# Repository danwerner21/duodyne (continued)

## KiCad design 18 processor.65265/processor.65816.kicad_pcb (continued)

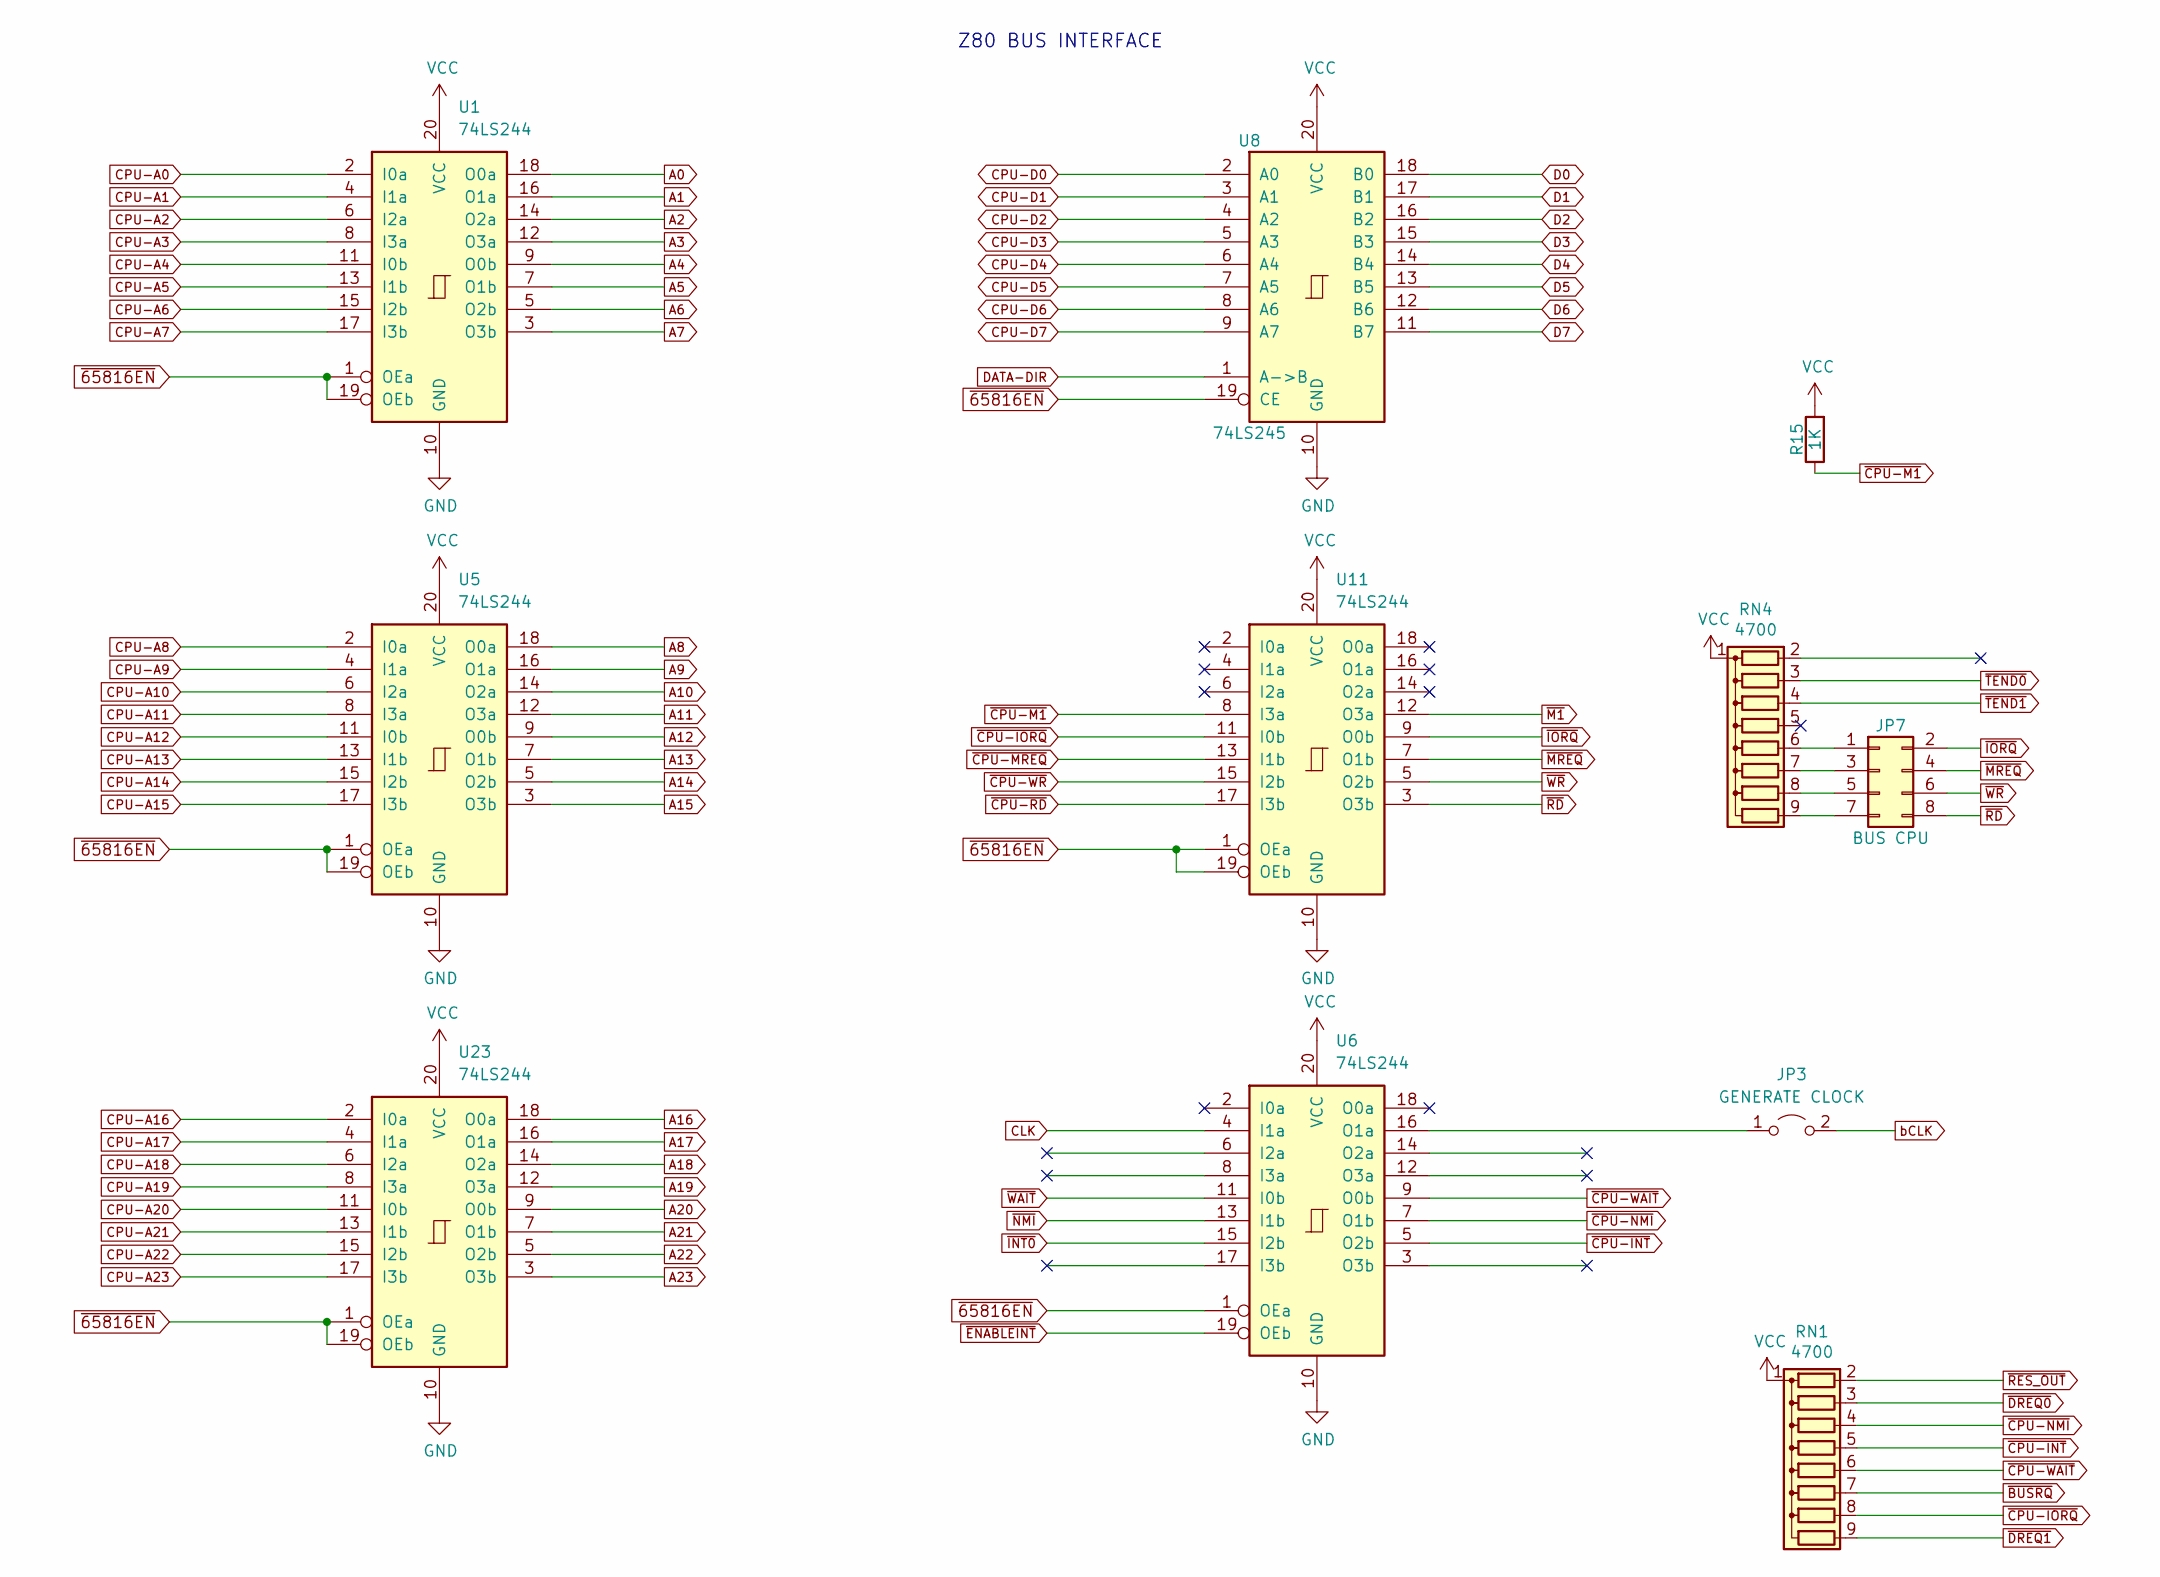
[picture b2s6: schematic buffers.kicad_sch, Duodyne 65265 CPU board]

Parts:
JP3: GENERATE CLOCK; PinHeader_1x02_P2.54mm_Vertical
JP7: BUS CPU; PinHeader_2x04_P2.54mm_Vertical
R15: 1K; R_Axial_DIN0207_L6.3mm_D2.5mm_P7.62mm_Horizontal
RN1, RN4: 4700; R_Array_SIP9
U1, U5, U6, U11, U23: 74LS244; DIP-20_W7.62mm_Socket_LongPads
U8: 74LS245; DIP-20_W7.62mm_Socket_LongPads

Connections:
A0: U1.18 (O0a); also elsewhere on the board
A1: U1.16 (O1a); also elsewhere on the board
A2: U1.14 (O2a); also elsewhere on the board
A3: U1.12 (O3a); also elsewhere on the board
A4: U1.9 (O0b); also elsewhere on the board
A5: U1.7 (O1b); also elsewhere on the board
A6: U1.5 (O2b); also elsewhere on the board
A7: U1.3 (O3b); also elsewhere on the board
A8: U5.18 (O0a); also elsewhere on the board
A9: U5.16 (O1a); also elsewhere on the board
A10: U5.14 (O2a); also elsewhere on the board
A11: U5.12 (O3a); also elsewhere on the board
A12: U5.9 (O0b); also elsewhere on the board
A13: U5.7 (O1b); also elsewhere on the board
A14: U5.5 (O2b); also elsewhere on the board
A15: U5.3 (O3b); also elsewhere on the board
A16: U23.18 (O0a); also elsewhere on the board
A17: U23.16 (O1a); also elsewhere on the board
A18: U23.14 (O2a); also elsewhere on the board
A19: U23.12 (O3a); also elsewhere on the board
A20: U23.9 (O0b); also elsewhere on the board
A21: U23.7 (O1b); also elsewhere on the board
A22: U23.5 (O2b); also elsewhere on the board
A23: U23.3 (O3b); also elsewhere on the board
CLK: U6.4 (I1a); also elsewhere on the board
CPU-A0: U1.2 (I0a); also elsewhere on the board
CPU-A1: U1.4 (I1a); also elsewhere on the board
CPU-A2: U1.6 (I2a); also elsewhere on the board
CPU-A3: U1.8 (I3a); also elsewhere on the board
CPU-A4: U1.11 (I0b); also elsewhere on the board
CPU-A5: U1.13 (I1b); also elsewhere on the board
CPU-A6: U1.15 (I2b); also elsewhere on the board
CPU-A7: U1.17 (I3b); also elsewhere on the board
CPU-A8: U5.2 (I0a); also elsewhere on the board
CPU-A9: U5.4 (I1a); also elsewhere on the board
CPU-A10: U5.6 (I2a); also elsewhere on the board
CPU-A11: U5.8 (I3a); also elsewhere on the board
CPU-A12: U5.11 (I0b); also elsewhere on the board
CPU-A13: U5.13 (I1b); also elsewhere on the board
CPU-A14: U5.15 (I2b); also elsewhere on the board
CPU-A15: U5.17 (I3b); also elsewhere on the board
CPU-A16: U23.2 (I0a); also elsewhere on the board
CPU-A17: U23.4 (I1a); also elsewhere on the board
CPU-A18: U23.6 (I2a); also elsewhere on the board
CPU-A19: U23.8 (I3a); also elsewhere on the board
CPU-A20: U23.11 (I0b); also elsewhere on the board
CPU-A21: U23.13 (I1b); also elsewhere on the board
CPU-A22: U23.15 (I2b); also elsewhere on the board
CPU-A23: U23.17 (I3b); also elsewhere on the board
CPU-D0: U8.2 (A0); also elsewhere on the board
CPU-D1: U8.3 (A1); also elsewhere on the board
CPU-D2: U8.4 (A2); also elsewhere on the board
CPU-D3: U8.5 (A3); also elsewhere on the board
CPU-D4: U8.6 (A4); also elsewhere on the board
CPU-D5: U8.7 (A5); also elsewhere on the board
CPU-D6: U8.8 (A6); also elsewhere on the board
CPU-D7: U8.9 (A7); also elsewhere on the board
D0: U8.18 (B0); also elsewhere on the board
D1: U8.17 (B1); also elsewhere on the board
D2: U8.16 (B2); also elsewhere on the board
D3: U8.15 (B3); also elsewhere on the board
D4: U8.14 (B4); also elsewhere on the board
D5: U8.13 (B5); also elsewhere on the board
D6: U8.12 (B6); also elsewhere on the board
D7: U8.11 (B7); also elsewhere on the board
DATA-DIR: U8.1 (A->B); also elsewhere on the board
GND: U1.10 (GND), U5.10 (GND), U6.10 (GND), U8.10 (GND), U11.10 (GND), U23.10 (GND); also elsewhere on the board
unnamed: JP3.1 (A), U6.16 (O1a)
unnamed: JP7.1, RN4.6 (R5)
unnamed: JP7.3, RN4.7 (R6)
unnamed: JP7.5, RN4.8 (R7)
unnamed: JP7.7, RN4.9 (R8)
VCC: R15.2, RN1.1 (common), RN4.1 (common), U1.20 (VCC), U5.20 (VCC), U6.20 (VCC), U8.20 (VCC), U11.20 (VCC), U23.20 (VCC); also elsewhere on the board
bCLK: JP3.2 (B); also elsewhere on the board
~65816EN: U1.1 (OEa), U1.19 (OEb), U5.1 (OEa), U5.19 (OEb), U6.1 (OEa), U8.19 (CE), U11.1 (OEa), U11.19 (OEb), U23.1 (OEa), U23.19 (OEb); also elsewhere on the board
~BUSRQ: RN1.7 (R6); also elsewhere on the board
~CPU-INT: RN1.5 (R4), U6.5 (O2b); also elsewhere on the board
~CPU-IORQ: RN1.8 (R7), U11.11 (I0b); also elsewhere on the board
~CPU-M1: R15.1, U11.8 (I3a)
~CPU-MREQ: U11.13 (I1b); also elsewhere on the board
~CPU-NMI: RN1.4 (R3), U6.7 (O1b); also elsewhere on the board
~CPU-RD: U11.17 (I3b); also elsewhere on the board
~CPU-WAIT: RN1.6 (R5), U6.9 (O0b)
~CPU-WR: U11.15 (I2b); also elsewhere on the board
~DREQ0: RN1.3 (R2); also elsewhere on the board
~DREQ1: RN1.9 (R8); also elsewhere on the board
~ENABLEINT: U6.19 (OEb); also elsewhere on the board
~INT0: U6.15 (I2b); also elsewhere on the board
~IORQ: JP7.2, U11.9 (O0b); also elsewhere on the board
~M1: U11.12 (O3a); also elsewhere on the board
~MREQ: JP7.4, U11.7 (O1b); also elsewhere on the board
~NMI: U6.13 (I1b); also elsewhere on the board
~RD: JP7.8, U11.3 (O3b); also elsewhere on the board
~RES_OUT: RN1.2 (R1); also elsewhere on the board
~TEND0: RN4.3 (R2); also elsewhere on the board
~TEND1: RN4.4 (R3); also elsewhere on the board
~WAIT: U6.11 (I0b); also elsewhere on the board
~WR: JP7.6, U11.5 (O2b); also elsewhere on the board

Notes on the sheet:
Z80 BUS INTERFACE

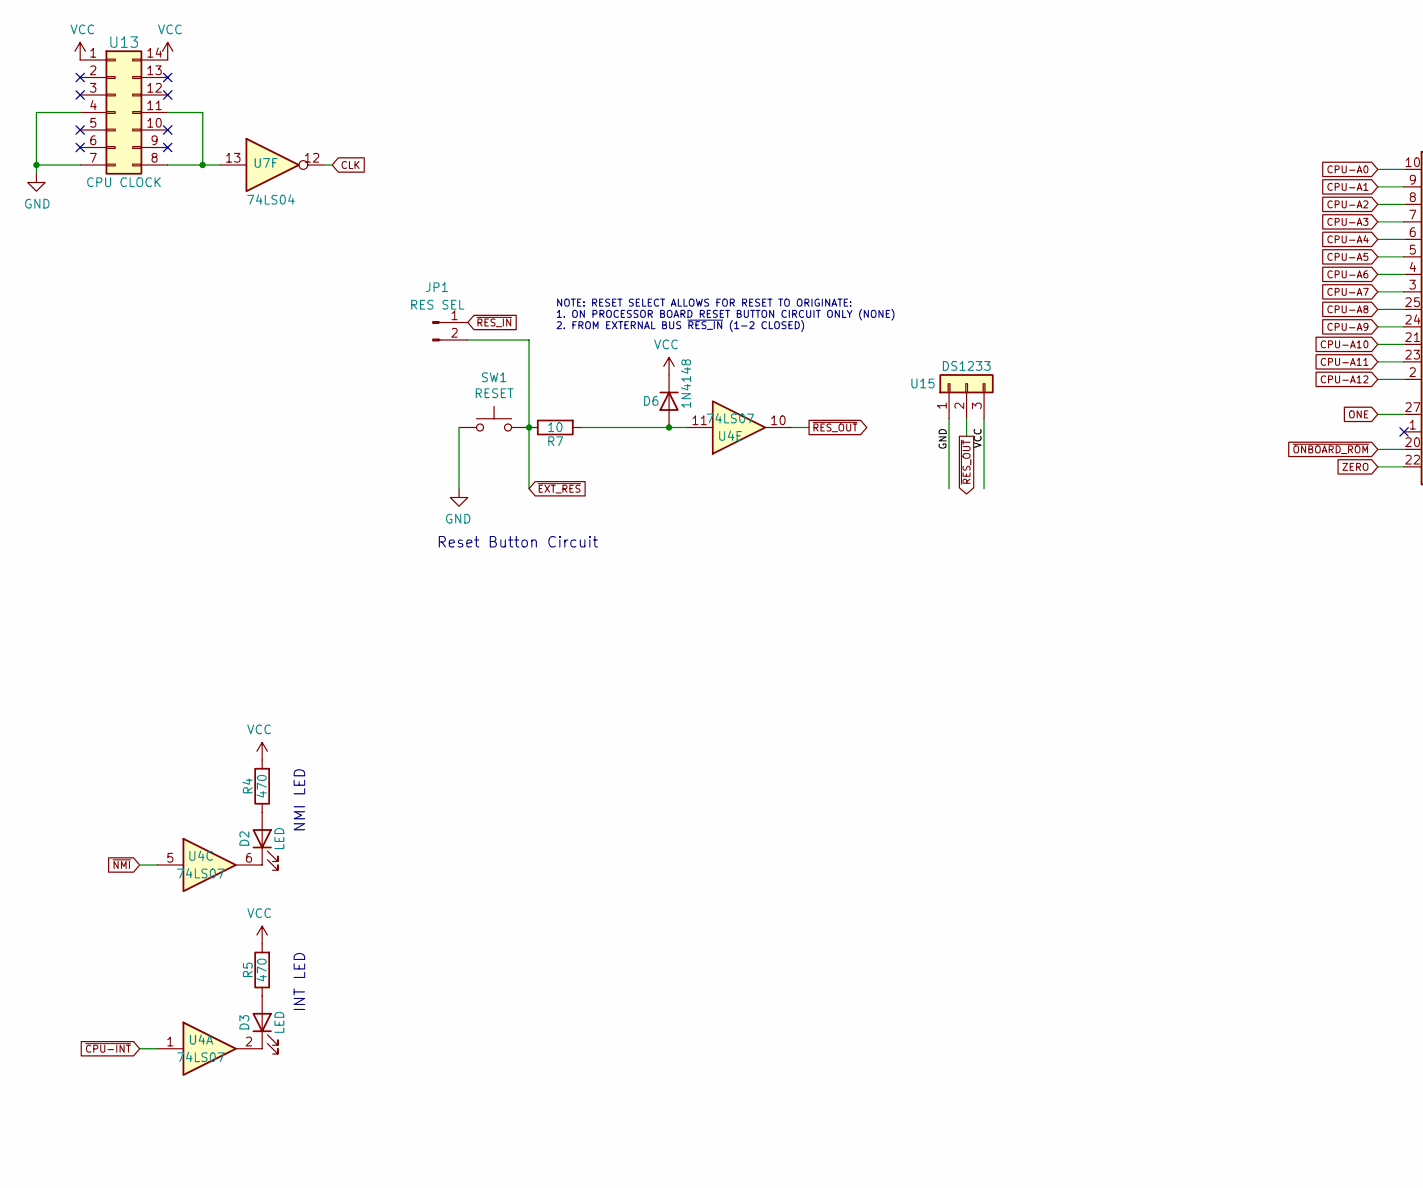
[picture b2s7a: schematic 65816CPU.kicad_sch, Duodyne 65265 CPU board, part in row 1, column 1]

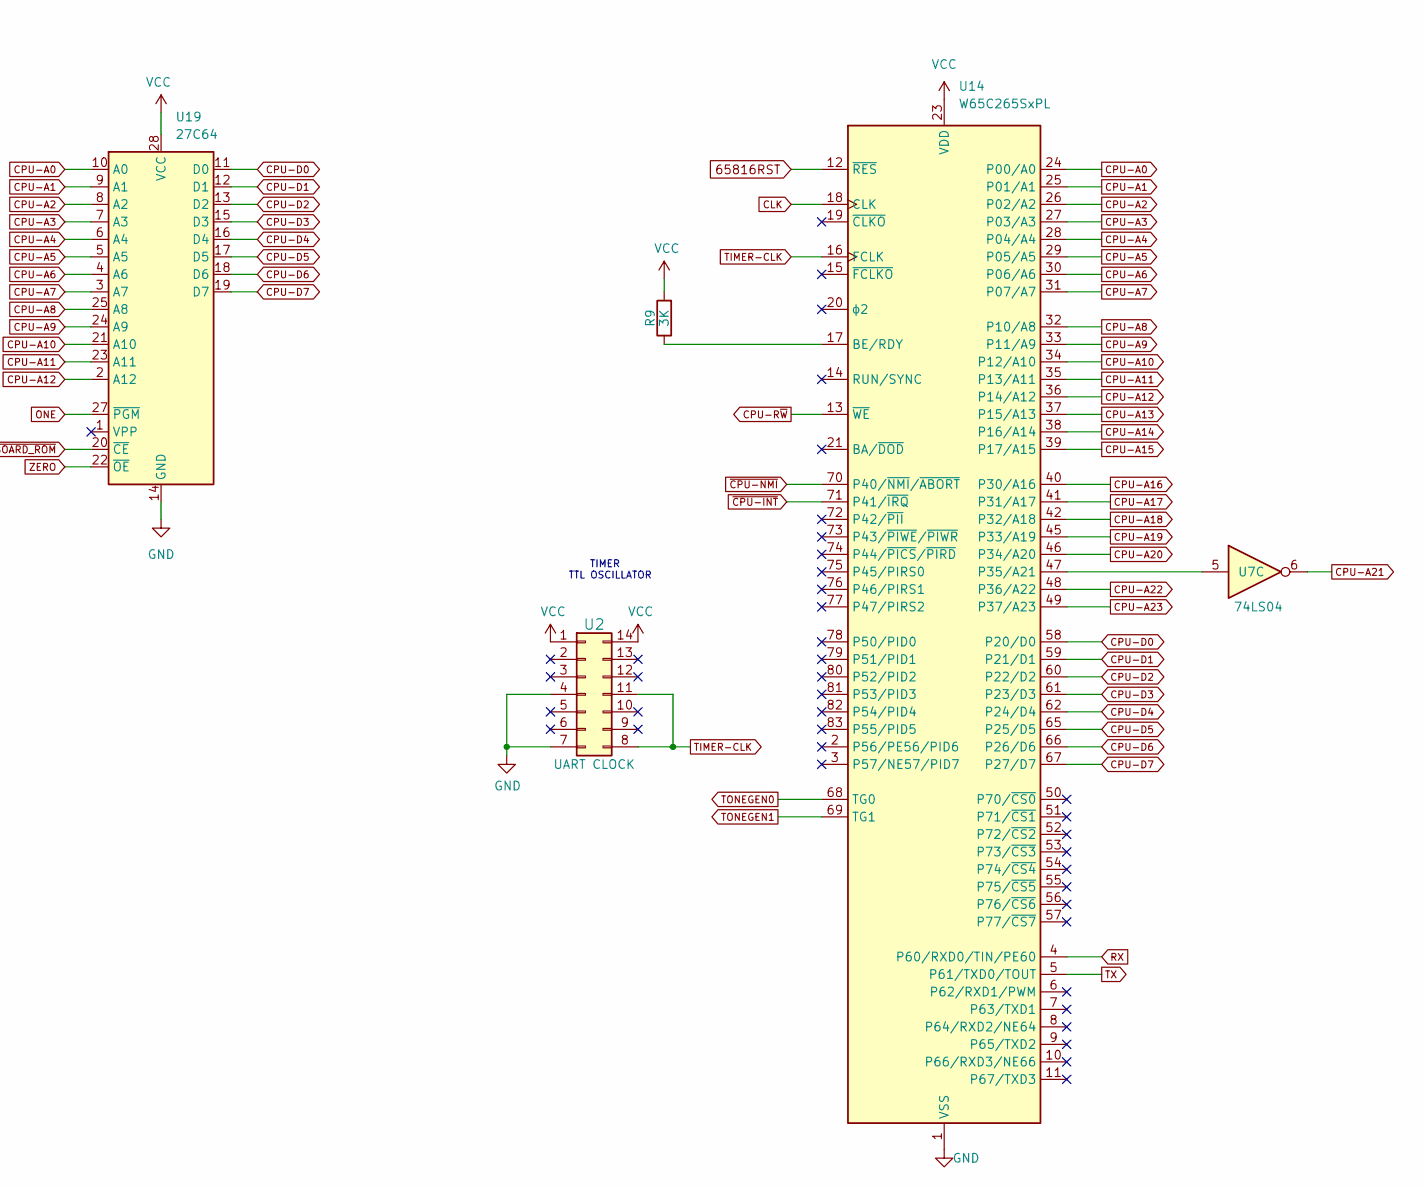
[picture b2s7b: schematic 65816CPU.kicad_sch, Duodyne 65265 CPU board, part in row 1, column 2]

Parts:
D2, D3: LED; LED_D3.0mm_Horizontal_O3.81mm_Z2.0mm
D6: 1N4148; D_DO-35_SOD27_P7.62mm_Horizontal
JP1: RES SEL; PinHeader_1x02_P2.54mm_Vertical
R4, R5: 470; R_Axial_DIN0207_L6.3mm_D2.5mm_P7.62mm_Horizontal
R7: 10; R_Axial_DIN0207_L6.3mm_D2.5mm_P7.62mm_Horizontal
R9: 3K; R_Axial_DIN0207_L6.3mm_D2.5mm_P7.62mm_Horizontal
SW1: RESET; SW_Tactile_SPST_Angled_PTS645Vx58-2LFS
U2: UART CLOCK; DIP-14_W7.62mm_Socket_LongPads
U4: 74LS07; DIP-14_W7.62mm_Socket_LongPads
U7: 74LS04; DIP-14_W7.62mm_Socket_LongPads
U13: CPU CLOCK; DIP-14_W7.62mm_Socket_LongPads
U14: W65C265SxPL; PLCC-84_THT-Socket
U15: DS1233; TO-92L_HandSolder
U19: 27C64; DIP-28_W15.24mm_Socket_LongPads

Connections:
65816RST: U14.12 (~RES); also elsewhere on the board
CLK: U7.12, U14.18 (CLK); also elsewhere on the board
CPU-A0: U14.24 (P00/A0), U19.10 (A0); also elsewhere on the board
CPU-A1: U14.25 (P01/A1), U19.9 (A1); also elsewhere on the board
CPU-A2: U14.26 (P02/A2), U19.8 (A2); also elsewhere on the board
CPU-A3: U14.27 (P03/A3), U19.7 (A3); also elsewhere on the board
CPU-A4: U14.28 (P04/A4), U19.6 (A4); also elsewhere on the board
CPU-A5: U14.29 (P05/A5), U19.5 (A5); also elsewhere on the board
CPU-A6: U14.30 (P06/A6), U19.4 (A6); also elsewhere on the board
CPU-A7: U14.31 (P07/A7), U19.3 (A7); also elsewhere on the board
CPU-A8: U14.32 (P10/A8), U19.25 (A8); also elsewhere on the board
CPU-A9: U14.33 (P11/A9), U19.24 (A9); also elsewhere on the board
CPU-A10: U14.34 (P12/A10), U19.21 (A10); also elsewhere on the board
CPU-A11: U14.35 (P13/A11), U19.23 (A11); also elsewhere on the board
CPU-A12: U14.36 (P14/A12), U19.2 (A12); also elsewhere on the board
CPU-A13: U14.37 (P15/A13); also elsewhere on the board
CPU-A14: U14.38 (P16/A14); also elsewhere on the board
CPU-A15: U14.39 (P17/A15); also elsewhere on the board
CPU-A16: U14.40 (P30/A16); also elsewhere on the board
CPU-A17: U14.41 (P31/A17); also elsewhere on the board
CPU-A18: U14.42 (P32/A18); also elsewhere on the board
CPU-A19: U14.45 (P33/A19); also elsewhere on the board
CPU-A20: U14.46 (P34/A20); also elsewhere on the board
CPU-A21: U7.6; also elsewhere on the board
CPU-A22: U14.48 (P36/A22); also elsewhere on the board
CPU-A23: U14.49 (P37/A23); also elsewhere on the board
CPU-D0: U14.58 (P20/D0), U19.11 (D0); also elsewhere on the board
CPU-D1: U14.59 (P21/D1), U19.12 (D1); also elsewhere on the board
CPU-D2: U14.60 (P22/D2), U19.13 (D2); also elsewhere on the board
CPU-D3: U14.61 (P23/D3), U19.15 (D3); also elsewhere on the board
CPU-D4: U14.62 (P24/D4), U19.16 (D4); also elsewhere on the board
CPU-D5: U14.65 (P25/D5), U19.17 (D5); also elsewhere on the board
CPU-D6: U14.66 (P26/D6), U19.18 (D6); also elsewhere on the board
CPU-D7: U14.67 (P27/D7), U19.19 (D7); also elsewhere on the board
CPU-R~W: U14.13 (~WE); also elsewhere on the board
GND: SW1.2, U2.4, U2.7, U13.4, U13.7, U14.1 (VSS), U14.22 (VSS), U14.43 (VSS), U14.64 (VSS), U15.1, U19.14 (GND); also elsewhere on the board
unnamed: D2.1 (K), U4.6
unnamed: D2.2 (A), R4.1
unnamed: D3.1 (K), U4.2
unnamed: D3.2 (A), R5.1
unnamed: D6.2 (A), R7.2, U4.11
unnamed: R9.1, U14.17 (BE/RDY)
unnamed: U7.13, U13.8, U13.11
unnamed: U7.5, U14.47 (P35/A21)
ONE: U19.27 (~PGM); also elsewhere on the board
RX: U14.4 (P60/RXD0/TIN/PE60); also elsewhere on the board
TIMER-CLK: U2.8, U2.11, U14.16 (FCLK)
TONEGEN0: U14.68 (TG0); also elsewhere on the board
TONEGEN1: U14.69 (TG1); also elsewhere on the board
TX: U14.5 (P61/TXD0/TOUT); also elsewhere on the board
VCC: D6.1 (K), R4.2, R5.2, R9.2, U2.1, U2.14, U13.1, U13.14, U14.23 (VDD), U14.44 (VDD), U14.63 (VDD), U14.84 (VDD), U15.3, U19.28 (VCC); also elsewhere on the board
ZERO: U19.22 (~OE); also elsewhere on the board
~CPU-INT: U4.1, U14.71 (P41/~IRQ); also elsewhere on the board
~CPU-NMI: U14.70 (P40/~NMI/~ABORT); also elsewhere on the board
~EXT_RES: JP1.2, R7.1, SW1.1; also elsewhere on the board
~NMI: U4.5; also elsewhere on the board
~ONBOARD_ROM: U19.20 (~CE); also elsewhere on the board
~RES_IN: JP1.1; also elsewhere on the board
~RES_OUT: U4.10, U15.2; also elsewhere on the board

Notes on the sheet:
Reset Button Circuit
NMI LED
INT LED
NOTE: RESET SELECT ALLOWS FOR RESET TO ORIGINATE: 1. ON PROCESSOR BOARD RESET BUTTON CIRCUIT ONLY (NONE) 2. FROM EXTERNAL BUS ~{RES_IN} (1-2 CLOSED)
TIMER TTL OSCILLATOR

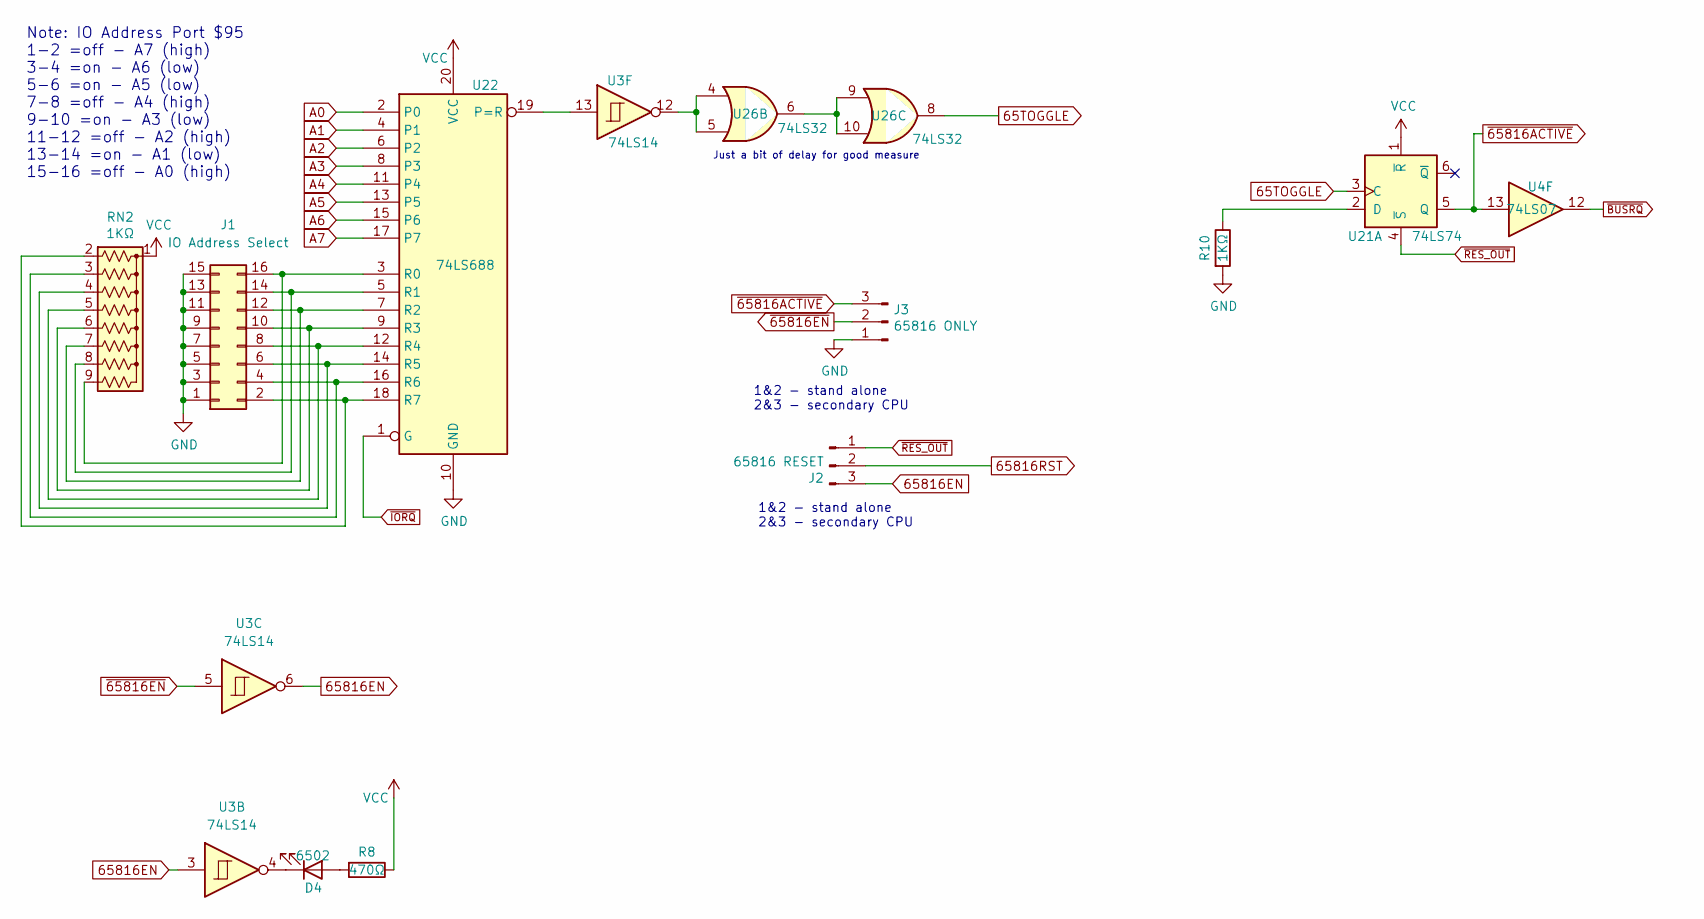
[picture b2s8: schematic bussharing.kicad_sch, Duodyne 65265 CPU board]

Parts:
D4: 6502; LED_D3.0mm_Horizontal_O3.81mm_Z2.0mm
J1: IO Address Select; PinHeader_2x08_P2.54mm_Vertical
J2: 65816 RESET; PinHeader_1x03_P2.54mm_Horizontal
J3: 65816 ONLY; PinHeader_1x03_P2.54mm_Horizontal
R8: 470Ω; R_Axial_DIN0207_L6.3mm_D2.5mm_P7.62mm_Horizontal
R10: 1KΩ; R_Axial_DIN0207_L6.3mm_D2.5mm_P7.62mm_Horizontal
RN2: 1KΩ; R_Array_SIP9
U3: 74LS14; DIP-14_W7.62mm_Socket_LongPads
U4: 74LS07; DIP-14_W7.62mm_Socket_LongPads
U21: 74LS74; DIP-14_W7.62mm_Socket_LongPads
U22: 74LS688; DIP-20_W7.62mm_Socket_LongPads
U26: 74LS32; DIP-14_W7.62mm_Socket_LongPads

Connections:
65TOGGLE: U21.3 (C), U26.8
65816EN: J2.3, U3.3, U3.6
65816RST: J2.2; also elsewhere on the board
A0: U22.2 (P0); also elsewhere on the board
A1: U22.4 (P1); also elsewhere on the board
A2: U22.6 (P2); also elsewhere on the board
A3: U22.8 (P3); also elsewhere on the board
A4: U22.11 (P4); also elsewhere on the board
A5: U22.13 (P5); also elsewhere on the board
A6: U22.15 (P6); also elsewhere on the board
A7: U22.17 (P7); also elsewhere on the board
GND: J1.1, J1.3, J1.5, J1.7, J1.9, J1.11, J1.13, J1.15, J3.1, R10.2, U22.10 (GND); also elsewhere on the board
unnamed: D4.1 (K), U3.4
unnamed: D4.2 (A), R8.2
unnamed: J1.2, RN2.2 (R1), U22.18 (R7)
unnamed: J1.4, RN2.3 (R2), U22.16 (R6)
unnamed: J1.6, RN2.4 (R3), U22.14 (R5)
unnamed: J1.8, RN2.5 (R4), U22.12 (R4)
unnamed: J1.10, RN2.6 (R5), U22.9 (R3)
unnamed: J1.12, RN2.7 (R6), U22.7 (R2)
unnamed: J1.14, RN2.8 (R7), U22.5 (R1)
unnamed: J1.16, RN2.9 (R8), U22.3 (R0)
unnamed: R10.1, U21.2 (D)
unnamed: U3.13, U22.19 (P=R)
unnamed: U3.12, U26.4, U26.5
unnamed: U26.6, U26.9, U26.10
VCC: R8.1, RN2.1 (common), U21.1 (~R), U22.20 (VCC); also elsewhere on the board
~65816ACTIVE: J3.3, U4.13, U21.5 (Q)
~65816EN: J3.2, U3.5; also elsewhere on the board
~BUSRQ: U4.12; also elsewhere on the board
~IORQ: U22.1 (G); also elsewhere on the board
~RES_OUT: J2.1, U21.4 (~S); also elsewhere on the board

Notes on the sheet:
1&2 - stand alone 2&3 - secondary CPU
Note: IO Address Port $95 1-2 =off - A7 (high) 3-4 =on - A6 (low) 5-6 =on - A5 (low) 7-8 =off - A4 (high) 9-10 =on - A3 (low) 11-12 =off - A2 (high) 13-14 =on - A1 (low) 15-16 =off - A0 (high)
Just a bit of delay for good measure

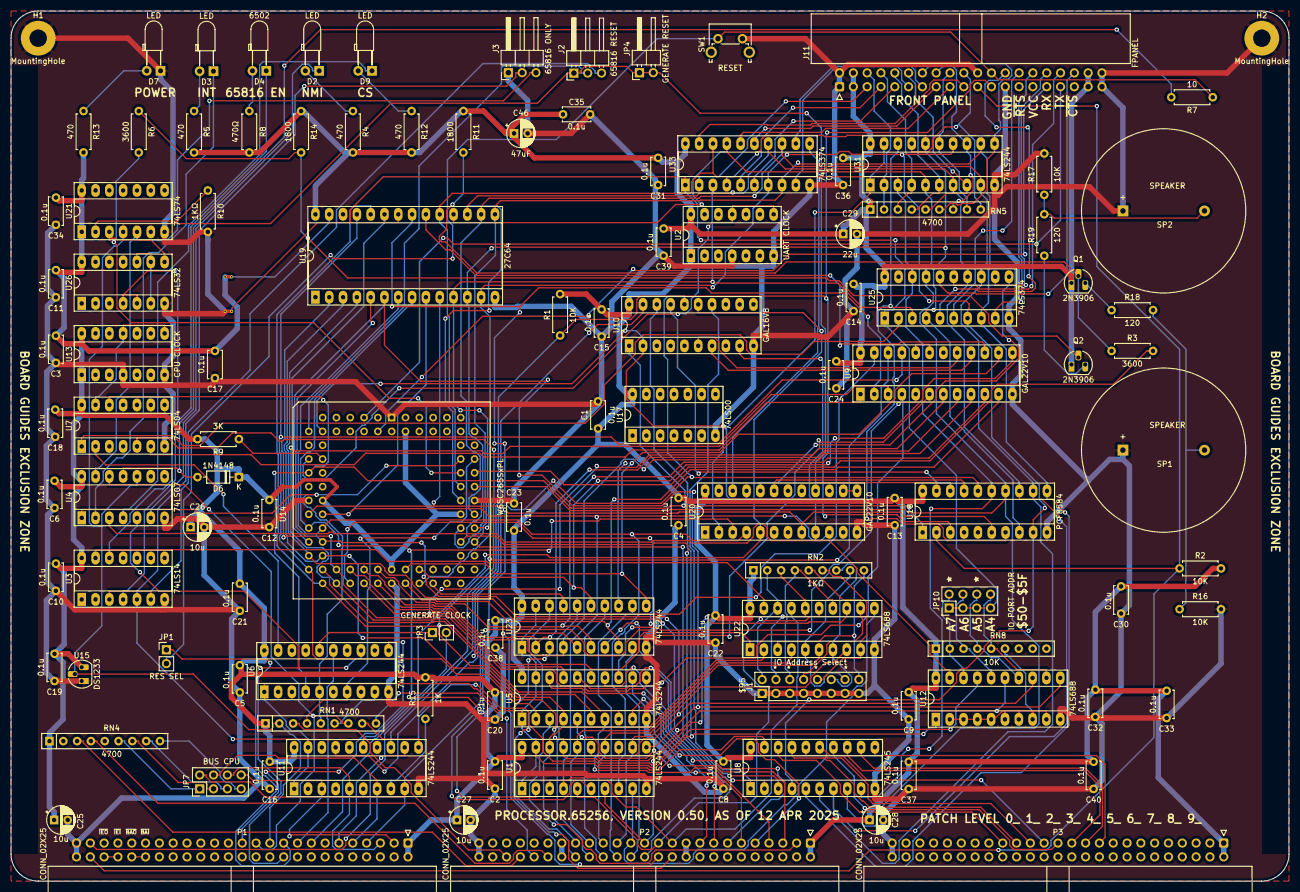
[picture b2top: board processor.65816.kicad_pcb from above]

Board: 2 copper layers, 235.0 x 160.0 mm, 117 parts (0 on the bottom side), 188 nets.
